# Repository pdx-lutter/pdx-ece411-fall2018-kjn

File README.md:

# Portland State University

## ECE 411 Practicum Project - Group 16

### Precision Temperature Control Unit

### Group Members

* Nathan Lutterman  
* Kimball Davis  
* Jason Houlihan  

### What is it?

Our group is designing and building a temperature control unit.  In a nutshell, the device reads some ambient temperature from a temperature sensor.  If the temperature being read is outside of some bound, above or blow, the device activates and utilizes a fan or a lamp (as a heater) respectively.

It's intended to be a small, portable temperature control unit.  The user interface consists of several 7-segment digital displays which are used as feedback for the user while inputting values for thresholds, as well as displaying the temperature being read.

### What's in it?

The device mostly charge is an AT89S52 8-bit microcontroller.  It'll be driving the 7-segment displays, reading the data from the temperature sensor, and triggering the relays for the fan and lamp.

---

### Important Documents

[Preliminary EAGLE PCB Design Schematic](docs/schematics/preliminary.sch)

### Licenses
SDCC suite is a collection of several components derived from different sources with different licenses.  

All project shared libraries used and provided by sdcc are under the GPL with the following exception:

>   As a special exception, if you link this library with other files,
>   some of which are compiled with SDCC, to produce an executable,
>   this library does not by itself cause the resulting executable to
>   be covered by the GNU General Public License. This exception does
>   not however invalidate any other reasons why the executable file
>   might be covered by the GNU General Public License.

The following is from the sdcc manual (found [here](http://sdcc.sourceforge.net/doc/sdccman.pdf)):

> – sdcc compiler:
> sdcc compiler is licensed under the GPLv2.
> The code or object files generated by SDCC suite are not licensed, so they can be used in FLOSS or
> proprietary (closed source) applications.
> 
> – dcpp preprocessor:
> derived from GCC cpp preprocessor http://gcc.gnu.org/; GPLv3 license
> 
> – sdas assemblers and sdld linker:
> derived from ASXXXX http://shop-pdp.kent.edu/ashtml/asxxxx.htm;
> license
> 
> – SDCC run-time libraries:
> The great majority of SDCC run-time libraries are licensed under the GPLv2+LE which allows linking
> of SDCC run-time libraries with proprietary (closed source) applications.
> Exception are pic device libraries and header files which are derived from Microchip header (.inc) and
> linker script (.lkr) files. Microchip requires that "The header files should state that they are only to
> be used with authentic Microchip devices" which makes them incompatible with the GPL. Pic device
> libraries and header files are located at non-free/lib and non-free/include directories respectively. SDCC
> should be run with the --use-non-free command line option in order to include non-free header files and
> libraries.
> 
> – sdbinutils utilities (sdar, sdranlib, sdnm, sdobjcopy):
> derived from GNU Binutils http://www.gnu.org/software/binutils/; GPLv3 license
> 
> – sdcclib librarian:
> GPLv2 license
> 
> – ucsim simulators:
> GPLv2 license
> 
> – sdcdb debugger:
> GPLv2 license
> 
> – gcc-test regression tests:
> derived from gcc-testsuite; no license explicitely specified, but since it is a part of GCC is probably
> GPLv3 licensed
> 
> – packihx:
> public domain
> 
> – makebin:
> zlib/libpng License
> 
> • libraries:
> – dbuf library:
> zlib/libpng License
> – Boost C++ libraries:
> http://www.boost.org/; Boost Software License 1.0 (BSL-1.0)
> Links to licenses:
> • GPLv2 license: http://www.gnu.org/licenses/old-licenses/gpl-2.0.html
> • LGPLv2.1 license: http://www.gnu.org/licenses/old-licenses/lgpl-2.1.html
> • GPLv3 license: http://www.gnu.org/licenses/gpl.html
> • zlib/libpng License: http://www.opensource.org/licenses/Zlib
> • Boost Software License 1.0 (BSL-1.0): http://www.opensource.org/licenses/BSL-1.0

The sdcc math.h and stdbool.h headers and libraries were used in the firmware of this project.

#### sdcc math.h License

   math.h: Floating point math function declarations

   Copyright (C) 2001, Jesus Calvino-Fraga, jesusc@ieee.org

   This library is free software; you can redistribute it and/or modify it
   under the terms of the GNU General Public License as published by the
   Free Software Foundation; either version 2, or (at your option) any
   later version.

   This library is distributed in the hope that it will be useful,
   but WITHOUT ANY WARRANTY; without even the implied warranty of
   MERCHANTABILITY or FITNESS FOR A PARTICULAR PURPOSE. See the
   GNU General Public License for more details.

   You should have received a copy of the GNU General Public License
   along with this library; see the file COPYING. If not, write to the
   Free Software Foundation, 51 Franklin Street, Fifth Floor, Boston,
   MA 02110-1301, USA.

   As a special exception, if you link this library with other files,
   some of which are compiled with SDCC, to produce an executable,
   this library does not by itself cause the resulting executable to
   be covered by the GNU General Public License. This exception does
   not however invalidate any other reasons why the executable file
   might be covered by the GNU General Public License.

#### sdcc stdbool.h

   stdbool.h - ANSI functions forward declarations

   Copyright (C) 2004, Maarten Brock, sourceforge.brock@dse.nl

   This library is free software; you can redistribute it and/or modify it
   under the terms of the GNU General Public License as published by the
   Free Software Foundation; either version 2, or (at your option) any
   later version.

   This library is distributed in the hope that it will be useful,
   but WITHOUT ANY WARRANTY; without even the implied warranty of
   MERCHANTABILITY or FITNESS FOR A PARTICULAR PURPOSE. See the
   GNU General Public License for more details.

   You should have received a copy of the GNU General Public License
   along with this library; see the file COPYING. If not, write to the
   Free Software Foundation, 51 Franklin Street, Fifth Floor, Boston,
   MA 02110-1301, USA.

   As a special exception, if you link this library with other files,
   some of which are compiled with SDCC, to produce an executable,
   this library does not by itself cause the resulting executable to
   be covered by the GNU General Public License. This exception does
   not however invalidate any other reasons why the executable file
   might be covered by the GNU General Public License.

#### 8051.h 

   8051.h: Register Declarations for the Intel 8051 Processor

   Copyright (C) 2000, Bela Torok / bela.torok@kssg.ch

   This library is free software; you can redistribute it and/or modify it
   under the terms of the GNU General Public License as published by the
   Free Software Foundation; either version 2, or (at your option) any
   later version.

   This library is distributed in the hope that it will be useful,
   but WITHOUT ANY WARRANTY; without even the implied warranty of
   MERCHANTABILITY or FITNESS FOR A PARTICULAR PURPOSE. See the
   GNU General Public License for more details.

   You should have received a copy of the GNU General Public License 
   along with this library; see the file COPYING. If not, write to the
   Free Software Foundation, 51 Franklin Street, Fifth Floor, Boston,
   MA 02110-1301, USA.

   As a special exception, if you link this library with other files,
   some of which are compiled with SDCC, to produce an executable,
   this library does not by itself cause the resulting executable to
   be covered by the GNU General Public License. This exception does
   not however invalidate any other reasons why the executable file
   might be covered by the GNU General Public License.

#### Circuit Schematic and PCB Layout Licensing

The work produced solely for this project, including the circuit diagram, PCB layout, and firmware is licensed under MIT.

Autodesk EAGLE was the CAD software used to produce both the circuit diagrams and the PCB layout design.

Autodesk EAGLE and other Autodesk trademarks may be found here: https://www.autodesk.com/company/legal-notices-trademarks/trademarks/autodesk-inc#top

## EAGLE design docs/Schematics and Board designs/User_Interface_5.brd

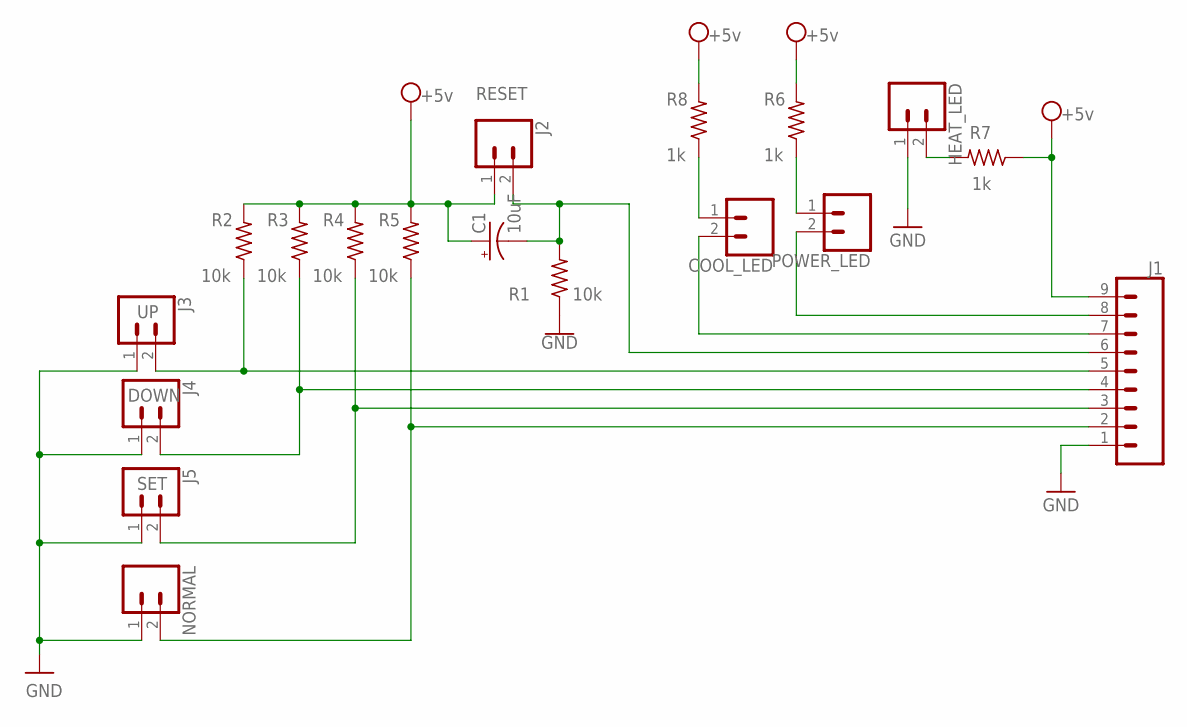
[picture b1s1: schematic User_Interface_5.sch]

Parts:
C1: 10uF; CPOL-RADIAL-2.5MM-5MM
COOL_LED: CONN_02; 1X02
HEAT_LED: CONN_02; 1X02
J1: CONN_09; 1X09
J2: RESET; 1X02
J3: UP; 1X02
J4: DOWN; 1X02
J5: SET; 1X02
NORMAL: CONN_02; 1X02
POWER_LED: CONN_02; 1X02
R1, R2, R3, R4, R5: 10k; R0603
R6, R7, R8: 1k; R0603

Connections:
GND: HEAT_LED.1, J1.1, J3.1, J4.1, J5.1, NORMAL.1, R1.1
unnamed: COOL_LED.1, R8.1
unnamed: J1.8, POWER_LED.2
unnamed: COOL_LED.2, J1.7
unnamed: J1.5, J3.2, R2.1
unnamed: J1.4, J4.2, R3.1
unnamed: J1.3, J5.2, R4.1
unnamed: J1.2, NORMAL.2, R5.1
unnamed: POWER_LED.1, R6.1
unnamed: HEAT_LED.2, R7.2
RST: C1.2 (-), J1.6, J2.2, R1.2
VCC: C1.1 (+), J1.9, J2.1, R2.2, R3.2, R4.2, R5.2, R6.2, R7.1, R8.2

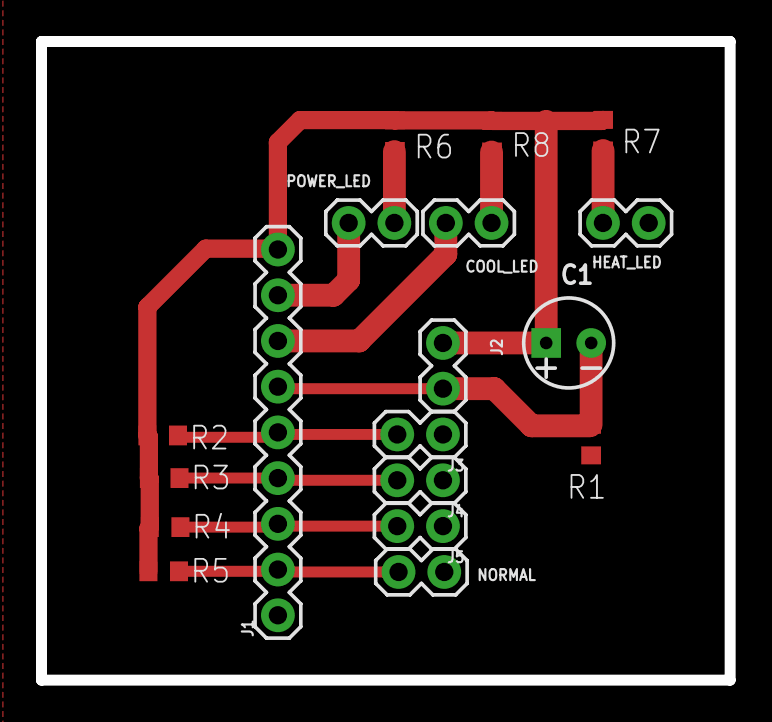
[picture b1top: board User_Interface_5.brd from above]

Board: 2 copper layers, 38.3 x 35.5 mm, 18 parts (0 on the bottom side), 12 nets.

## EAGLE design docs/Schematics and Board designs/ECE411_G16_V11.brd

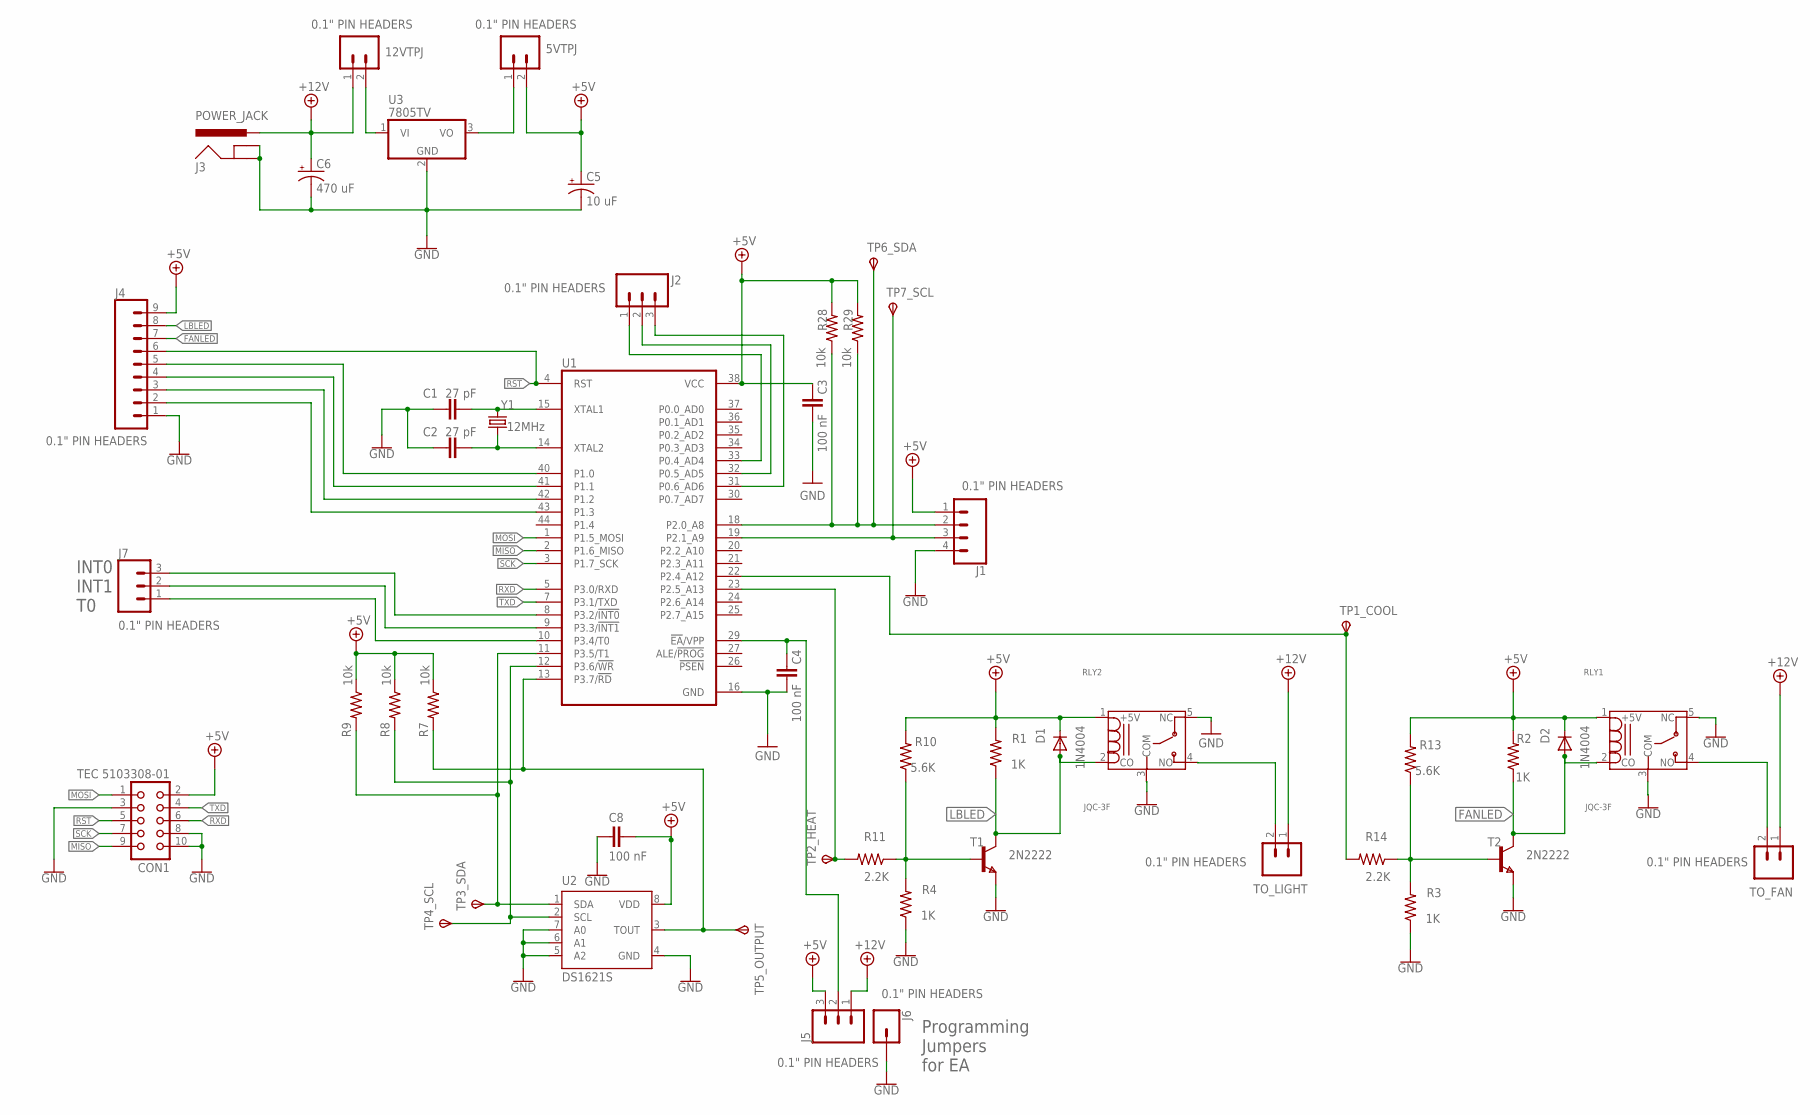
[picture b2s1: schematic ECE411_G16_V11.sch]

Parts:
5VTPJ, 12VTPJ: 0.1" PIN HEADERS; 1X02
C1, C2: 27 pF; RESC0603_M
C3, C4, C8: 100 nF; RESC0603_M
C5: 10 uF; TT2D6
C6: 470 uF; TT5D11
CON1: TEC 5103308-01; CON10
D1, D2: 1N4004; DO41-10
J1: 0.1" PIN HEADERS; 1X04
J2, J5, J7: 0.1" PIN HEADERS; 1X03
J3: POWER_JACK; POWER_JACK_PTH
J4: 0.1" PIN HEADERS; 1X09
J6: 0.1" PIN HEADERS; 1X01
R1, R2, R3, R4: 1K; R0603
R7, R8, R9, R28, R29: 10k; R0603
R10, R13: 5.6K; R0603
R11, R14: 2.2K; R0603
RLY1, RLY2: JQC-3F; T073
T1, T2: 2N2222; SOT-23
TO_FAN: 0.1" PIN HEADERS; 1X02
TO_LIGHT: 0.1" PIN HEADERS; 1X02
TP1_COOL, TP2_HEAT, TP3_SDA, TP4_SCL, TP5_OUTPUT, TP6_SDA, TP7_SCL: TPSTP20SQ; TP20SQ
U1: AT89S52; TQFP44
U2: DS1621S; SO08
U3: 7805TV; TO220V
Y1: 12MHz; CRYSTAL-SMD-5X3.2-4PAD

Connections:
+5V: 5VTPJ.2, C3.2, C5.+, C8.2, CON1.2, D1.C, D2.C, J1.1, J4.9, J5.3, R1.2, R2.2, R7.1, R8.1, R9.1, R10.2, R13.2, R28.2, R29.2, RLY1.1 (+5V), RLY2.1 (+5V), U1.38 (VCC), U2.8 (VDD)
+12V: 12VTPJ.1, C6.+, J3.PWR, J5.1, TO_FAN.1, TO_LIGHT.1
FANLED: D2.A, J4.7, R2.1, RLY1.2 (CO), T2.1 (C)
GND: C1.1, C2.1, C3.1, C4.1, C5.-, C6.-, C8.1, CON1.3, CON1.8, CON1.10, J1.4, J3.GND, J3.GNDBREAK, J4.1, J6.1, R3.1, R4.1, RLY1.3 (COM), RLY1.5 (NC), RLY2.3 (COM), RLY2.5 (NC), T1.2 (E), T2.2 (E), U1.16 (GND), U1.17 (GND), U2.4 (GND), U2.5 (A2), U2.6 (A1), U2.7 (A0), U3.2 (GND)
LBLED: D1.A, J4.8, R1.1, RLY2.2 (CO), T1.1 (C)
MISO: CON1.9, U1.2 (P1.6_MISO)
MOSI: CON1.1, U1.1 (P1.5_MOSI)
unnamed: C1.2, U1.15 (XTAL1), Y1.1
unnamed: C2.2, U1.14 (XTAL2), Y1.3 (2)
unnamed: J1.2, R28.1, R29.1, TP6_SDA.TP, U1.18 (P2.0_A8)
unnamed: J1.3, TP7_SCL.TP, U1.19 (P2.1_A9)
unnamed: 12VTPJ.2, U3.1 (VI)
unnamed: 5VTPJ.1, U3.3 (VO)
unnamed: RLY2.4 (NO), TO_LIGHT.2
unnamed: C4.2, J5.2, U1.29 (!EA!/VPP)
unnamed: R7.2, TP5_OUTPUT.TP, U1.13 (P3.7/!RD), U2.3 (TOUT)
unnamed: R8.2, TP4_SCL.TP, U1.12 (P3.6/!WR), U2.2 (SCL)
unnamed: R9.2, TP3_SDA.TP, U1.11 (P3.5/T1), U2.1 (SDA)
unnamed: R11.2, TP2_HEAT.TP, U1.23 (P2.5_A13)
unnamed: R4.2, R10.1, R11.1, T1.3 (B)
unnamed: J2.1, U1.33 (P0.4_AD4)
unnamed: J2.2, U1.32 (P0.5_AD5)
unnamed: R14.2, TP1_COOL.TP, U1.22 (P2.4_A12)
unnamed: R3.2, R13.1, R14.1, T2.3 (B)
unnamed: J2.3, U1.31 (P0.6_AD6)
unnamed: RLY1.4 (NO), TO_FAN.2
unnamed: J7.3, U1.8 (P3.2/!INT0)
unnamed: J7.2, U1.9 (P3.3/!INT1)
unnamed: J7.1, U1.10 (P3.4/T0)
unnamed: J4.5, U1.40 (P1.0)
unnamed: J4.4, U1.41 (P1.1)
unnamed: J4.3, U1.42 (P1.2)
unnamed: J4.2, U1.43 (P1.3)
RST: CON1.5, J4.6, U1.4 (RST)
RXD: CON1.6, U1.5 (P3.0/RXD)
SCK: CON1.7, U1.3 (P1.7_SCK)
TXD: CON1.4, U1.7 (P3.1/TXD)

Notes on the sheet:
Programming Jumpers for EA
INT0 INT1 T0

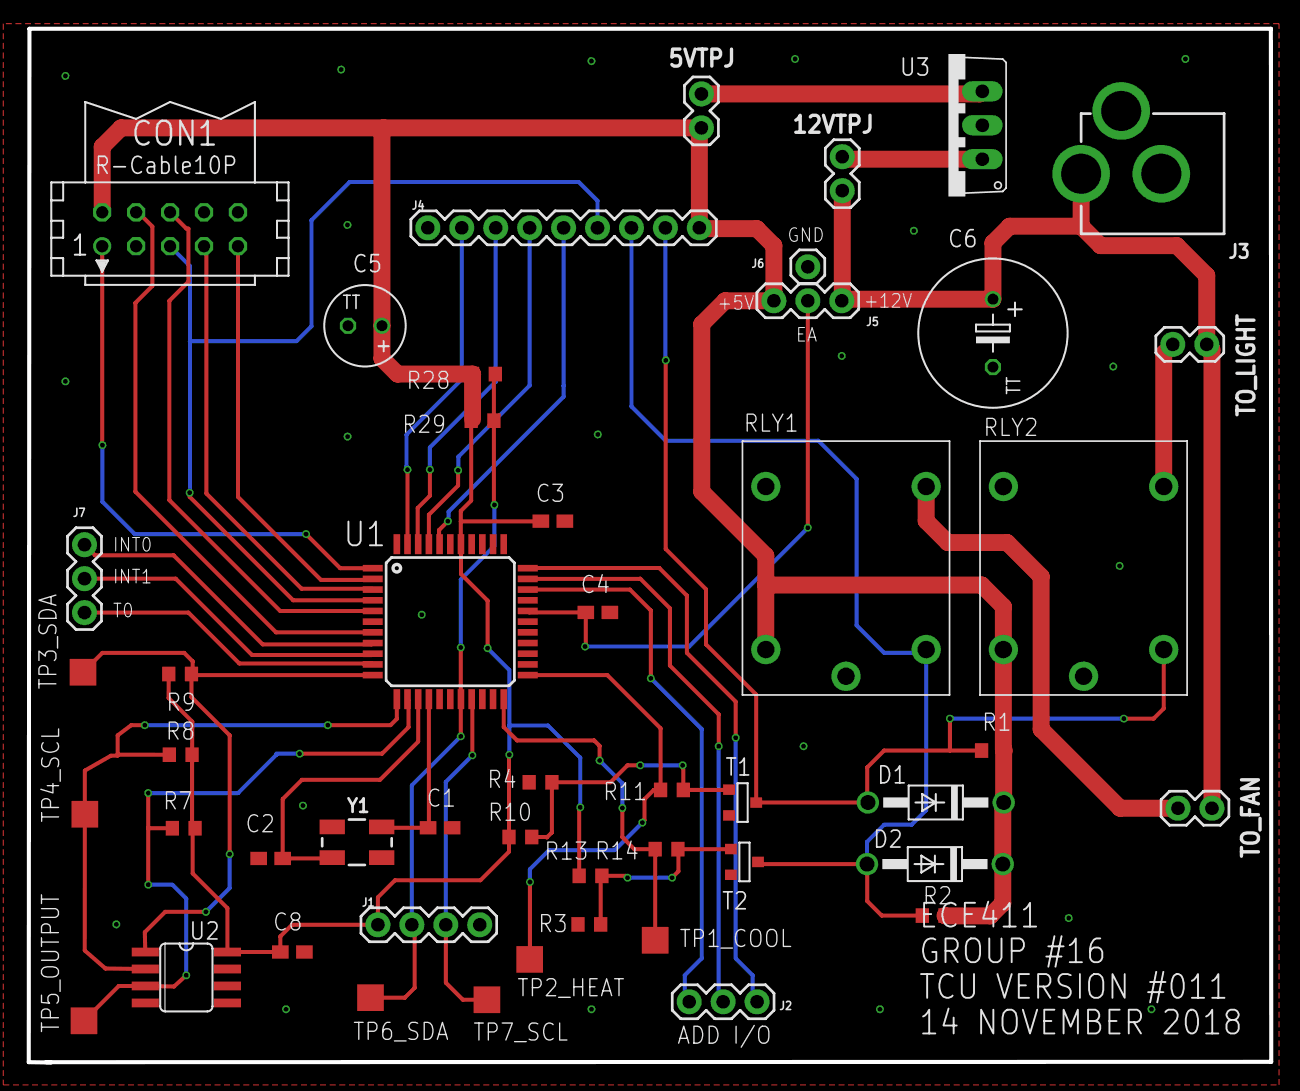
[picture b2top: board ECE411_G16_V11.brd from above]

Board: 2 copper layers, 93.0 x 77.4 mm, 49 parts (0 on the bottom side), 37 nets.

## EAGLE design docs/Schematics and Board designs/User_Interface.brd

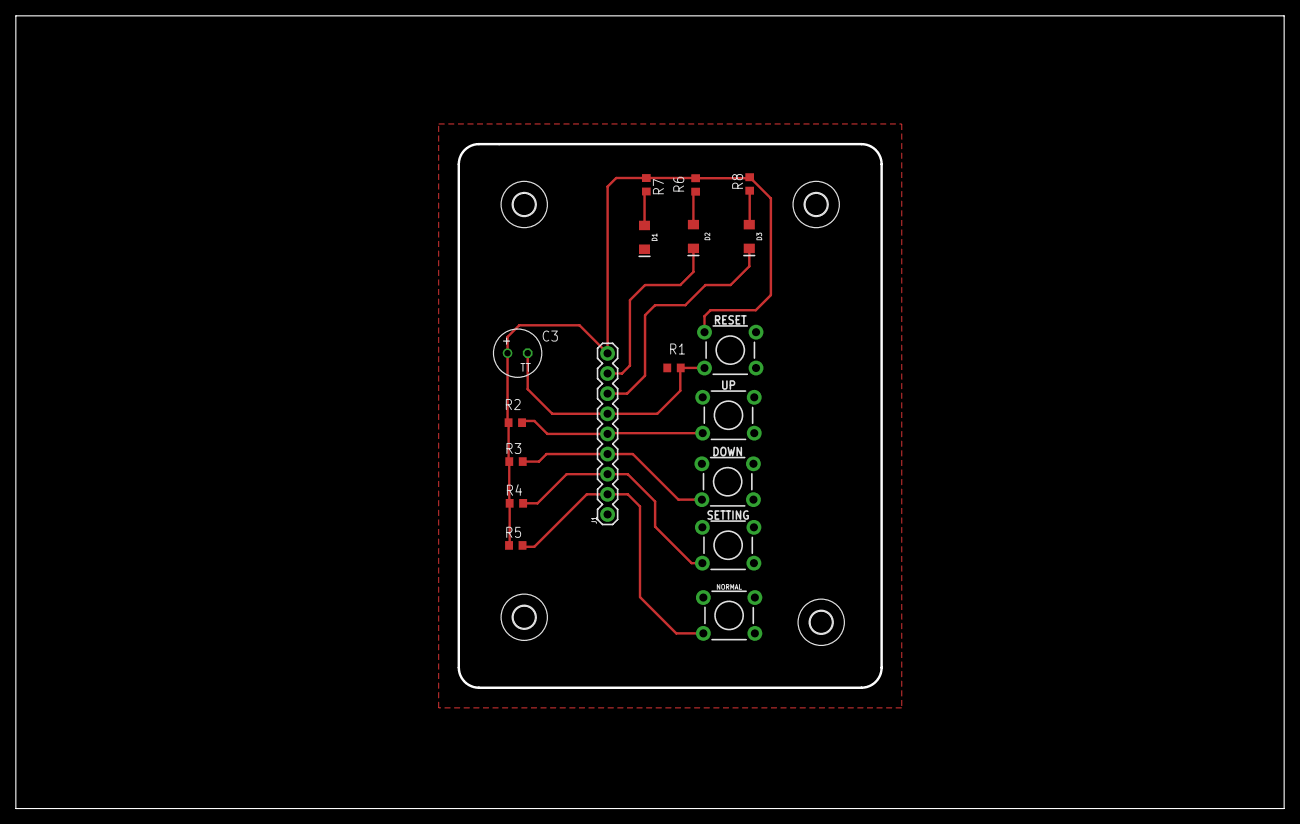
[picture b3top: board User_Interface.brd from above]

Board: 2 copper layers, 160.0 x 100.0 mm, 22 parts (0 on the bottom side), 12 nets.

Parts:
C3: 10 uF; TT2D6
D1: GREEN; LED-1206
D2: RED; LED-1206
D3: BLUE; LED-1206
DOWN: TACTILE_SWITCH_PTH_6.0MM
H1, H2, H3, H4: MOUNT-HOLE2.8; 2,8
J1: 1X09
NORMAL: TACTILE_SWITCH_PTH_6.0MM
R1, R2, R3, R4, R5: 10k; R0603
R6, R7, R8: 1k; R0603
RESET: TACTILE_SWITCH_PTH_6.0MM
SETTING: TACTILE_SWITCH_PTH_6.0MM
UP: TACTILE_SWITCH_PTH_6.0MM

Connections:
GND: D1.C, DOWN.1, J1.1, NORMAL.1, R1.1, SETTING.1, UP.1
unnamed: D1.A, R7.2
unnamed: D2.C, J1.8
unnamed: D3.C, J1.7
unnamed: J1.5, R2.1, UP.3
unnamed: DOWN.3, J1.4, R3.1
unnamed: J1.3, R4.1, SETTING.3
unnamed: J1.2, NORMAL.3, R5.1
unnamed: D2.A, R6.1
unnamed: D3.A, R8.1
RST: C3.-, J1.6, R1.2, RESET.3
VCC: C3.+, J1.9, R2.2, R3.2, R4.2, R5.2, R6.2, R7.1, R8.2, RESET.1

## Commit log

2018-10-10 Update README.md
    Added group members
2018-10-10 Update README.md
    Formatting
2018-10-11 Added index.html for starting github pages
2018-10-11 Set theme jekyll-theme-slate
2018-10-11 Updated README to show group #
2018-10-25 Add additional directories for documentation Add log files to .gitignore Include list of ordered parts (experimental or otherwise)
2018-10-25 Include link to GitHub pages site
2018-10-25 Add additional documentation, schematics, data sheets; Update README
2018-10-25 Add small image for prelim schematic
2018-10-25 Add a little more context to what the project is from the README
2018-10-25 Rename pds directory for context; Small formatting changes to PDS document
2018-10-25 Correctly render LaTeX document as image
2018-10-25 Format README
2018-10-28 Update pds.tex
    deleted a picture from an old report. just testing this
2018-10-28 Update pds.tex
    Some small edits, also streamlined the requirements.
2018-10-29 Update PDS Small formatting and spacing changes
2018-10-29 Compile PDS LaTeX document
2018-11-01 Add version 5 of TCU schematic and board layout
2018-11-01 Edited component name and value locations
2018-11-01 uploaded tcu board V2 image
2018-11-01 chagned file names
2018-11-02 Added bypass caps and test points
2018-11-03 added user interface schematic and board, added some images
2018-11-07 added tex for design review notes
2018-11-07 Post design review version 7
2018-11-07 tidying up
2018-11-07 added images
2018-11-13 Added V8 shcematic and board images
2018-11-13 Added .schem and .brd for V8
    Added test jumpers at +12 V
    Added Jumpers for fan and light
    Added additional I/O pins
    Added bypass cap for DS1621
    Moved power supply
    General redesign
2018-11-14 Added "final" versions of schematic and board
2018-11-15 THE final versions of schematic and PCB
2018-11-23 Added test plan 1
2018-11-27 Added V011 images
2018-11-29 Add data sheets for the 7-segment LED display, its controller, and the USB ASP
2018-11-29 Add 8051 manual
2018-11-29 Add schematic for 7-seg display with backpack
2018-11-29 Add (incomplete) test plan for checking that output of DS1621 matches output of AT89S52 to LED display
2018-11-29 Added test plan 2
2018-12-03 Create ECE411_TP3_G16 (2).xlsx
    File conflict. Renamed Nathan's test plan 2 test plan 3
2018-12-04 Add display test code
2018-12-04 Add 8051 hardware manual as well as temperature sensor's I2C waveforms
2018-12-04 Add 8051 header file, provided by sdcc
2018-12-04 Add 8051 instruction set manual and sdcc manual
2018-12-04 Add data sheet explaining higher resolution capture for DS1620
2018-12-04 Add code for gathering and displaying temperature from sensor to 7 seg display
2018-12-05 Removed docs on wrong part (sorry :P)
2018-12-05 Add avrdude configuration which includes at89s52 definition
2018-12-05 Adjust gitignore
2018-12-05 Clean up temp reading method, remove assignment op from macro
2018-12-05 Update src structure a little
2018-12-06 Add source files in new path
2018-12-06 Added relay/button testing code
2018-12-06 Update License information on README
2018-12-06 Add sdcc header/library usage licenses and additional information for Autodesk EAGLE
2018-12-06 Add addtional information about GNU public license with proprietary usage exception
2018-12-06 Remove link to unused public github.io page
2018-12-06 the end

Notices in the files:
parts and their libraries:
SparkFun-Connectors: Licensing: Creative Commons ShareAlike 4.0 International - https://creativecommons.org/licenses/by-sa/4.0
